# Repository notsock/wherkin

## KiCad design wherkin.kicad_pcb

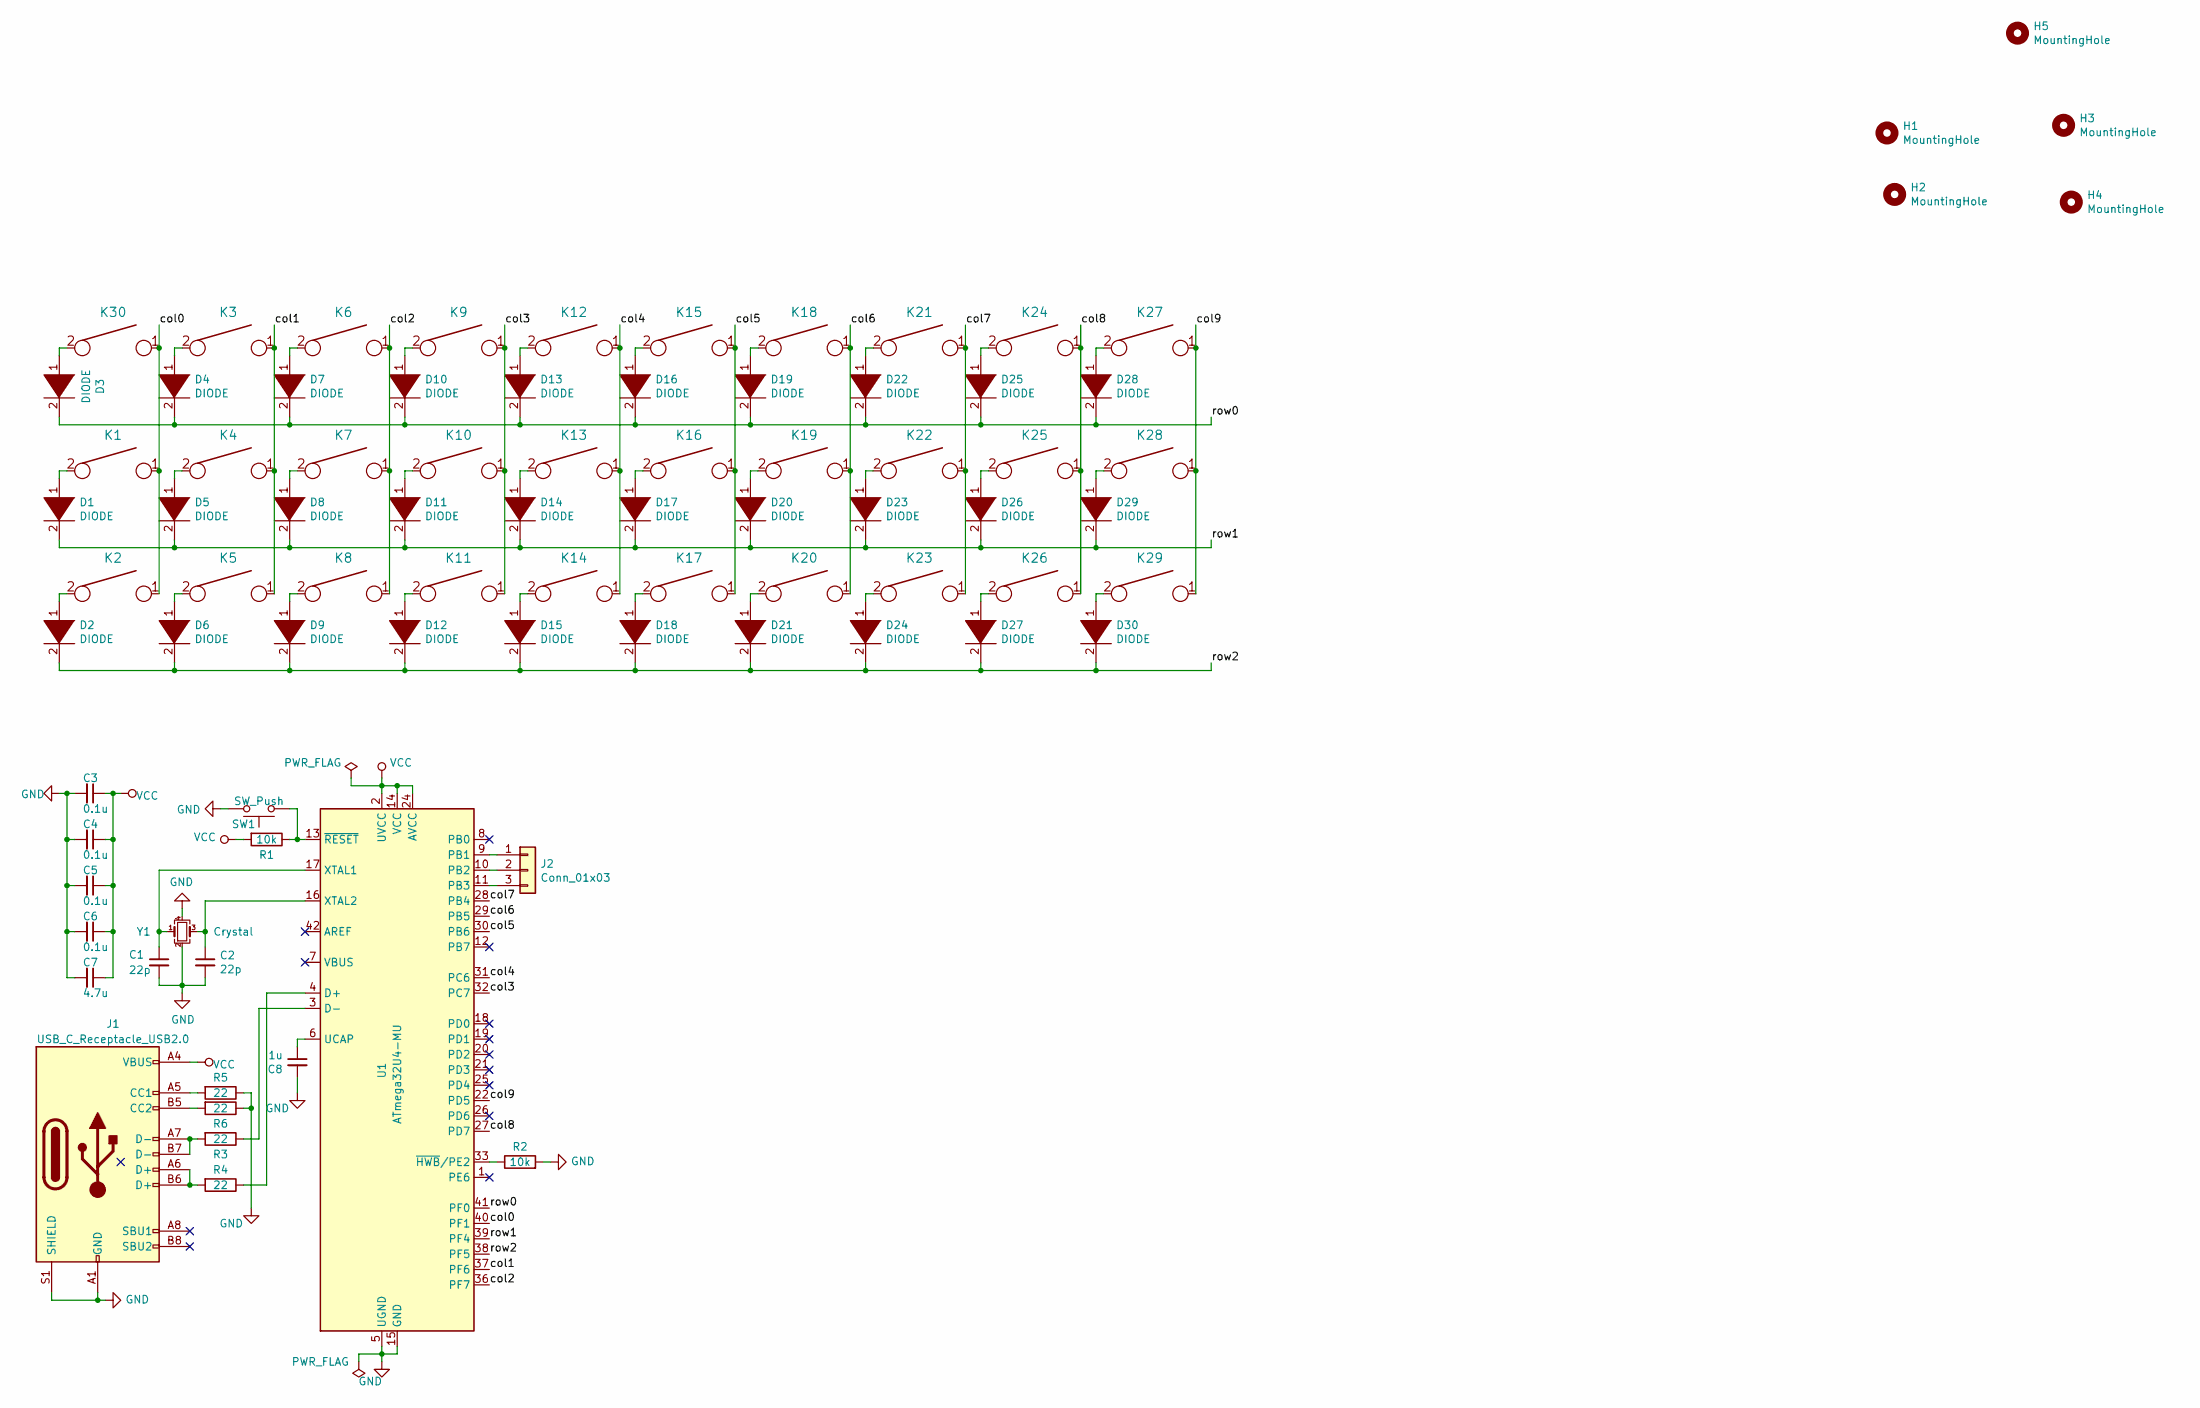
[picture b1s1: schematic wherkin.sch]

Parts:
C1, C2: 22p; C_0603_1608Metric_Pad1.05x0.95mm_HandSolder
C3, C4, C5, C6: 0.1u; C_0603_1608Metric_Pad1.05x0.95mm_HandSolder
C7: 4.7u; C_0603_1608Metric_Pad1.05x0.95mm_HandSolder
C8: 1u; C_0603_1608Metric_Pad1.05x0.95mm_HandSolder
D1, D2, D3, D4, D5, D6, D7, D8, D9, D10, D11, D12, D13, D14, D15, D16, D17, D18, D19, D20, D21, D22, D23, D24, D25, D26, D27, D28, D29, D30: DIODE; D_0201_0603Metric
H1, H2, H3, H4, H5: MountingHole; MountingHole_2.2mm_M2
J1: USB_C_Receptacle_USB2.0; USB_C_Receptacle_HRO_TYPE-C-31-M-12_hand_solder
J2: Conn_01x03; PinHeader_1x03_P1.00mm_Vertical
K1, K2, K3, K4, K5, K6, K7, K8, K9, K10, K11, K12, K13, K14, K15, K16, K17, K18, K19, K20, K21, K22, K23, K24, K25, K26, K27, K28, K29, K30: KEYSW; Kailh_socket_MX
R1, R2: 10k; R_0603_1608Metric_Pad1.05x0.95mm_HandSolder
R3, R4, R5, R6: 22; R_0603_1608Metric_Pad1.05x0.95mm_HandSolder
SW1: SW_Push; SW_Push_1P1T_NO_CK_KMR2
U1: ATmega32U4-MU; QFN-44-1EP_7x7mm_P0.5mm_EP5.2x5.2mm
Y1: Crystal; Crystal_SMD_3225-4Pin_3.2x2.5mm_HandSoldering

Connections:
/col0: K1.1, K2.1, K30.1, U1.40 (PF1)
/col1: K3.1, K4.1, K5.1, U1.37 (PF6)
/col2: K6.1, K7.1, K8.1, U1.36 (PF7)
/col3: K9.1, K10.1, K11.1, U1.32 (PC7)
/col4: K12.1, K13.1, K14.1, U1.31 (PC6)
/col5: K15.1, K16.1, K17.1, U1.30 (PB6)
/col6: K18.1, K19.1, K20.1, U1.29 (PB5)
/col7: K21.1, K22.1, K23.1, U1.28 (PB4)
/col8: K24.1, K25.1, K26.1, U1.27 (PD7)
/col9: K27.1, K28.1, K29.1, U1.22 (PD5)
/row0: D3.2 (A), D4.2 (A), D7.2 (A), D10.2 (A), D13.2 (A), D16.2 (A), D19.2 (A), D22.2 (A), D25.2 (A), D28.2 (A), U1.41 (PF0)
/row1: D1.2 (A), D5.2 (A), D8.2 (A), D11.2 (A), D14.2 (A), D17.2 (A), D20.2 (A), D23.2 (A), D26.2 (A), D29.2 (A), U1.39 (PF4)
/row2: D2.2 (A), D6.2 (A), D9.2 (A), D12.2 (A), D15.2 (A), D18.2 (A), D21.2 (A), D24.2 (A), D27.2 (A), D30.2 (A), U1.38 (PF5)
GND: C1.2, C2.2, C3.2, C4.2, C5.2, C6.2, C7.2, C8.2, J1.A1 (GND), J1.A12 (GND), J1.B1 (GND), J1.B12 (GND), J1.S1 (SHIELD), R2.2, R5.1, R6.1, SW1.2, U1.5 (UGND), U1.15 (GND), U1.23 (GND), U1.35 (GND), U1.43 (GND), U1.45 (GND), Y1.2, Y1.4
unnamed: C1.1, U1.17 (XTAL1), Y1.1
unnamed: C2.1, U1.16 (XTAL2), Y1.3
unnamed: C8.1, U1.6 (UCAP)
unnamed: D1.1 (K), K1.2
unnamed: D2.1 (K), K2.2
unnamed: D3.1 (K), K30.2
unnamed: D4.1 (K), K3.2
unnamed: D5.1 (K), K4.2
unnamed: D6.1 (K), K5.2
unnamed: D7.1 (K), K6.2
unnamed: D8.1 (K), K7.2
unnamed: D9.1 (K), K8.2
unnamed: D10.1 (K), K9.2
unnamed: D11.1 (K), K10.2
unnamed: D12.1 (K), K11.2
unnamed: D13.1 (K), K12.2
unnamed: D14.1 (K), K13.2
unnamed: D15.1 (K), K14.2
unnamed: D16.1 (K), K15.2
unnamed: D17.1 (K), K16.2
unnamed: D18.1 (K), K17.2
unnamed: D19.1 (K), K18.2
unnamed: D20.1 (K), K19.2
unnamed: D21.1 (K), K20.2
unnamed: D22.1 (K), K21.2
unnamed: D23.1 (K), K22.2
unnamed: D24.1 (K), K23.2
unnamed: D25.1 (K), K24.2
unnamed: D26.1 (K), K25.2
unnamed: D27.1 (K), K26.2
unnamed: D28.1 (K), K27.2
unnamed: D29.1 (K), K28.2
unnamed: D30.1 (K), K29.2
unnamed: J1.A5 (CC1), R5.2
unnamed: J1.A6 (D+), J1.B6 (D+), R4.2
unnamed: J1.A7 (D-), J1.B7 (D-), R3.2
unnamed: J1.B5 (CC2), R6.2
unnamed: J2.1, U1.9 (PB1)
unnamed: J2.2, U1.10 (PB2)
unnamed: J2.3, U1.11 (PB3)
unnamed: R1.1, SW1.1, U1.13 (~RESET)
unnamed: R2.1, U1.33 (~HWB~/PE2)
unnamed: R3.1, U1.3 (D-)
unnamed: R4.1, U1.4 (D+)
VCC: C3.1, C4.1, C5.1, C6.1, C7.1, J1.A4 (VBUS), J1.A9 (VBUS), J1.B4 (VBUS), J1.B9 (VBUS), R1.2, U1.2 (UVCC), U1.14 (VCC), U1.24 (AVCC), U1.34 (VCC), U1.44 (AVCC)

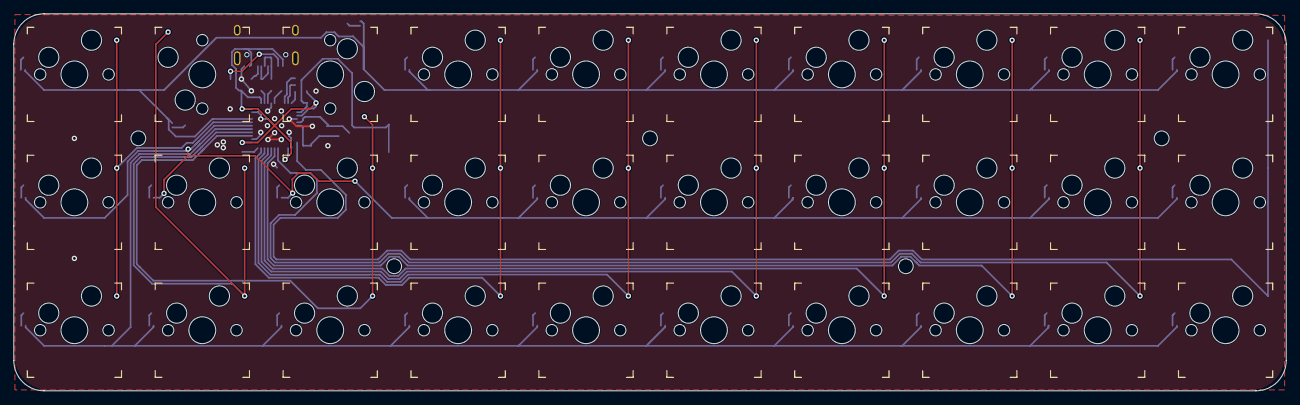
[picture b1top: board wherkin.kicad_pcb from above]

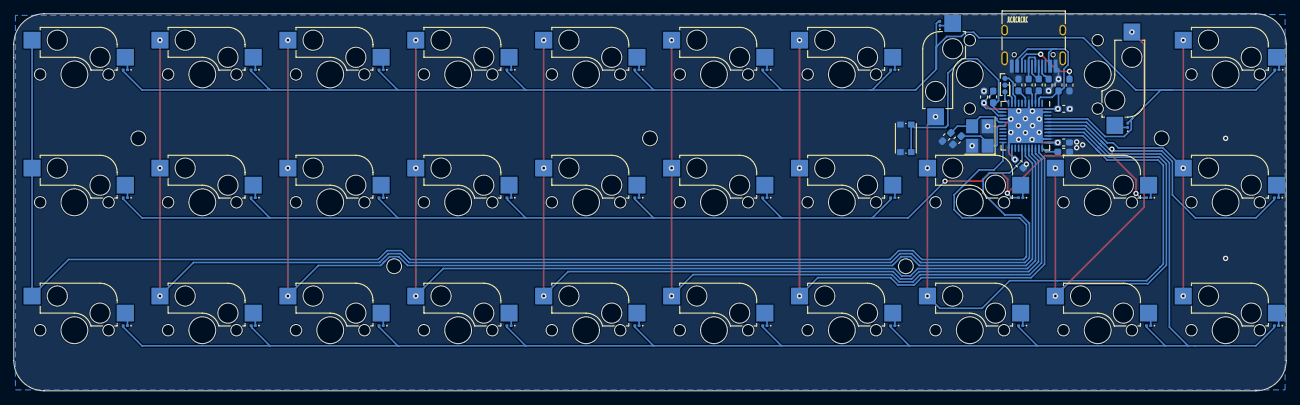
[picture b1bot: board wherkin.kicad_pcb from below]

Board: 2 copper layers, 189.0 x 56.0 mm, 84 parts (53 on the bottom side), 59 nets.

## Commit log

2021-04-21 rev1
